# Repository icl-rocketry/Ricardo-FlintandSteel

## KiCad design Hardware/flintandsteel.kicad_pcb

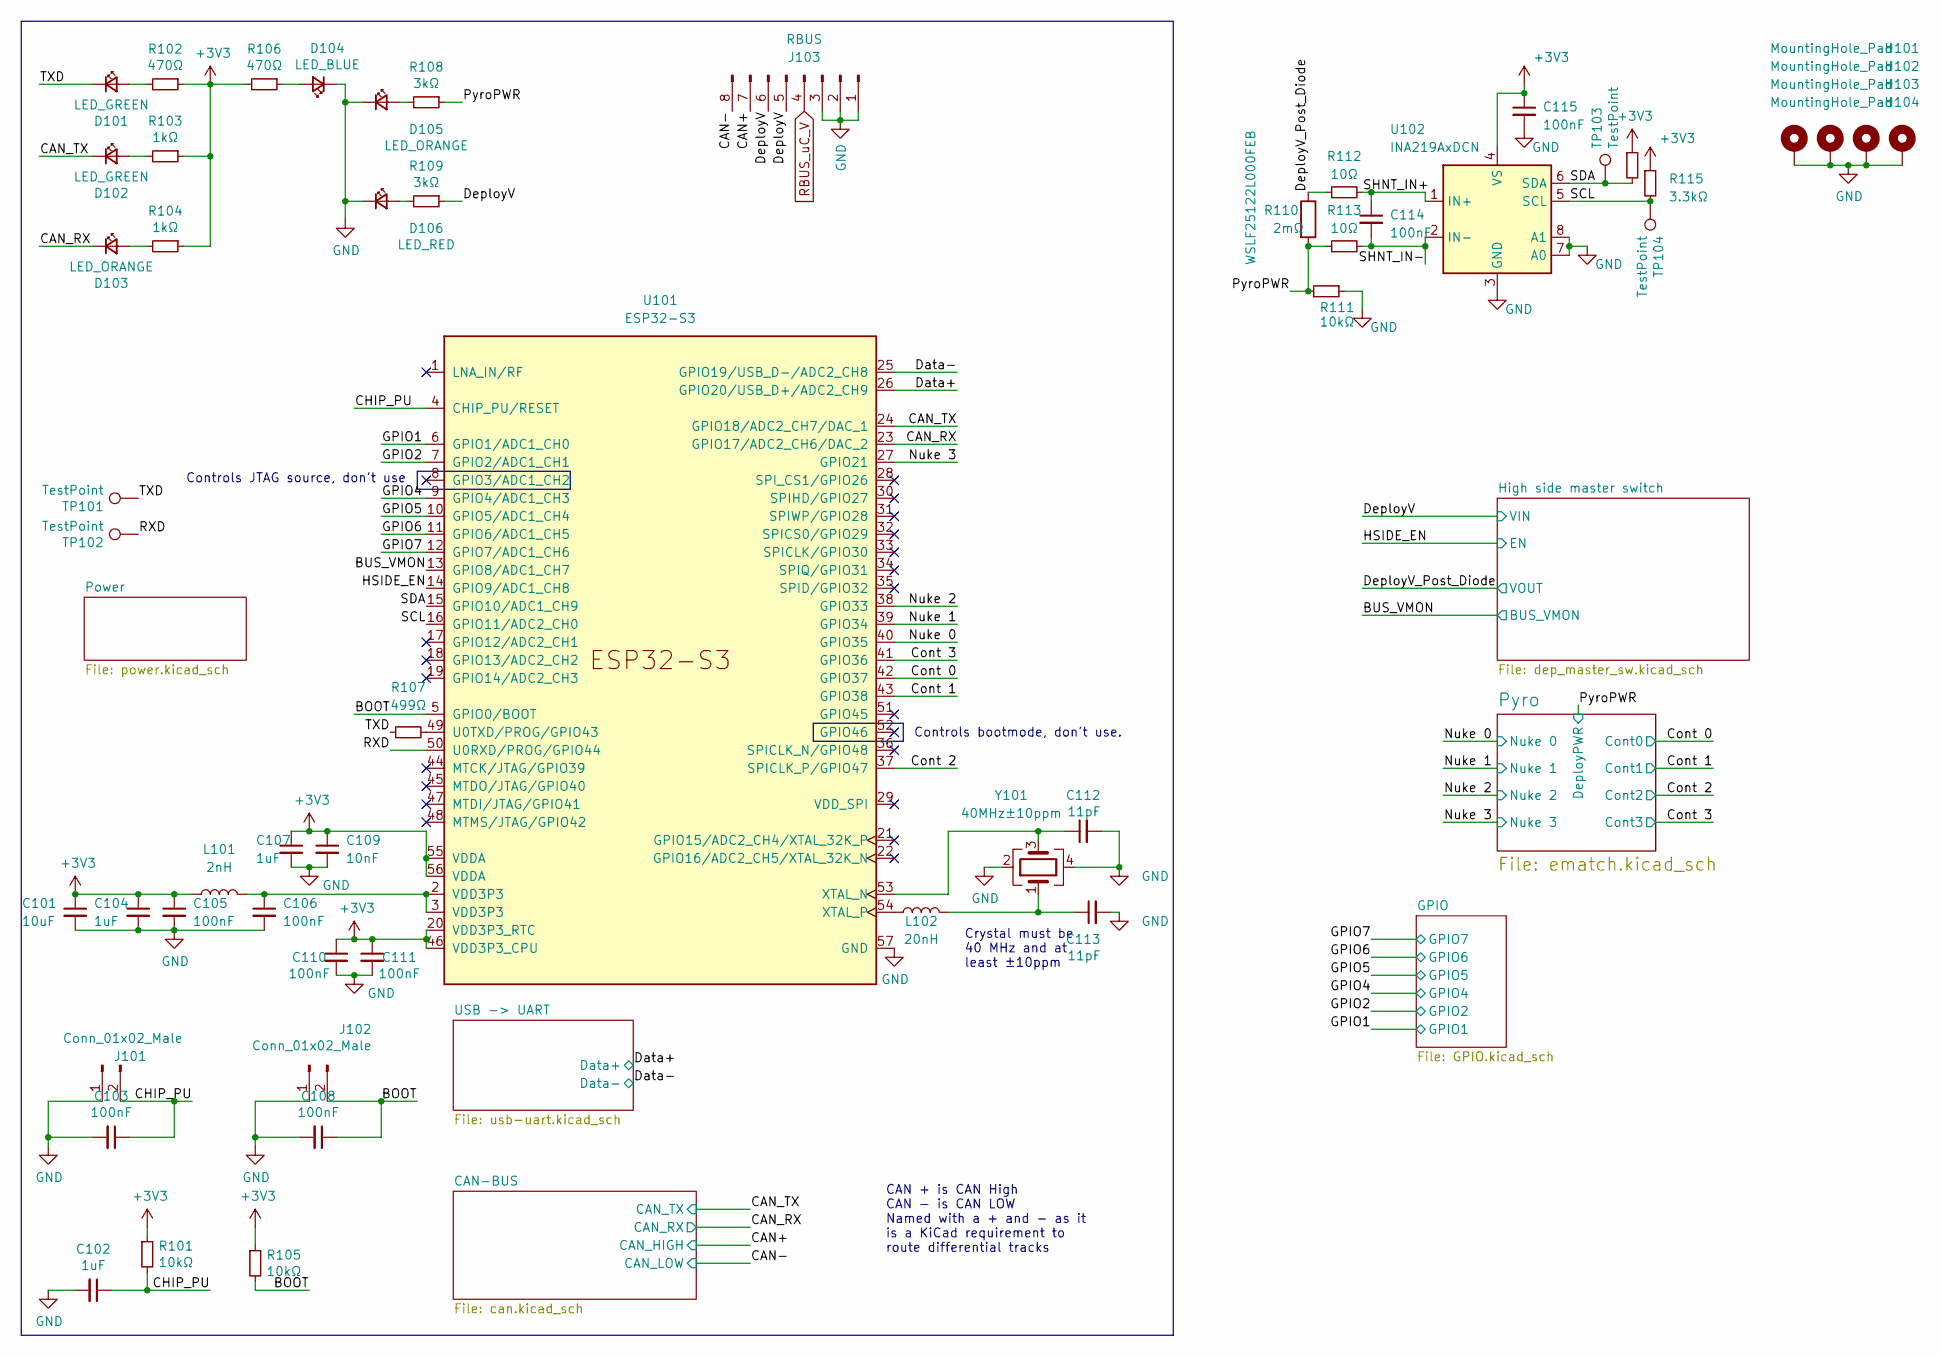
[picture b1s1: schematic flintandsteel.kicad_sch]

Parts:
C101: 10uF; C_0402_1005Metric
C102, C104, C107: 1uF; C_0402_1005Metric
C103, C105, C106, C108, C110, C111, C114, C115: 100nF; C_0402_1005Metric
C109: 10nF; C_0402_1005Metric
C112, C113: 11pF; C_0402_1005Metric
D101, D102: LED_GREEN; LED_0402_1005Metric
D103, D105: LED_ORANGE; LED_0402_1005Metric
D104: LED_BLUE; LED_0402_1005Metric
D106: LED_RED; LED_0402_1005Metric
H101, H102, H103, H104: MountingHole_Pad; MountingHole_3.2mm_M3_DIN965_Pad
J101, J102: Conn_01x02_Male; PinHeader_1x02_P2.54mm_Vertical
J103: RBUS; Molex_Mini-Fit_Jr_5569-08A2_2x04_P4.20mm_Horizontal
L101: 2nH; L_0402_1005Metric
L102: 20nH; L_0402_1005Metric
R101, R105, R111: 10kΩ; R_0402_1005Metric
R102, R106: 470Ω; R_0402_1005Metric
R103, R104: 1kΩ; R_0402_1005Metric
R107: 499Ω; R_0402_1005Metric; MPN AC0402FR-07499RL
R108, R109: 3kΩ; R_0402_1005Metric
R110: 2mΩ; R_2512_6332Metric_Pad1.40x3.35mm_HandSolder; MPN WSLF25122L000FEB
R112, R113: 10Ω; R_0402_1005Metric
R114, R115: 3.3kΩ; R_0402_1005Metric
TP101, TP102, TP103, TP104: TestPoint; TestPoint_Pad_D1.0mm
U101: ESP32-S3; QFN40P700X700X90-57N
U102: INA219AxDCN; SOT-23-8
Y101: 40MHz±10ppm; Crystal_SMD_2016-4Pin_2.0x1.6mm; MPN R940000171

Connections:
+3V3: C101.1, C104.1, C105.1, C107.1, C109.1, C110.1, C111.1, C115.1, L101.1, R101.1, R102.1, R103.1, R104.1, R105.1, R106.2, R114.1, R115.1, U101.20 (VDD3P3_RTC), U101.46 (VDD3P3_CPU), U101.55 (VDDA), U101.56 (VDDA), U102.4 (VS); also elsewhere on the board
/BOOT: C108.1, J102.2, R105.2, U101.5 (GPIO0/BOOT)
/BUS_VMON: U101.13 (GPIO8/ADC1_CH7); also elsewhere on the board
/CAN+: J103.7; also elsewhere on the board
/CAN-: J103.8; also elsewhere on the board
/CAN_RX: D103.1 (K), U101.23 (GPIO17/ADC2_CH6/DAC_2); also elsewhere on the board
/CAN_TX: D102.1 (K), U101.24 (GPIO18/ADC2_CH7/DAC_1); also elsewhere on the board
/CHIP_PU: C102.1, C103.1, J101.2, R101.2, U101.4 (CHIP_PU/RESET)
/Cont 0: U101.42 (GPIO37); also elsewhere on the board
/Cont 1: U101.43 (GPIO38); also elsewhere on the board
/Cont 2: U101.37 (SPICLK_P/GPIO47); also elsewhere on the board
/Cont 3: U101.41 (GPIO36); also elsewhere on the board
/Data+: U101.26 (GPIO20/USB_D+/ADC2_CH9); also elsewhere on the board
/Data-: U101.25 (GPIO19/USB_D-/ADC2_CH8); also elsewhere on the board
/DeployV: J103.5, J103.6, R109.1; also elsewhere on the board
/DeployV_Post_Diode: R110.1, R112.1; also elsewhere on the board
/GPIO1: U101.6 (GPIO1/ADC1_CH0); also elsewhere on the board
/GPIO2: U101.7 (GPIO2/ADC1_CH1); also elsewhere on the board
/GPIO4: U101.9 (GPIO4/ADC1_CH3); also elsewhere on the board
/GPIO5: U101.10 (GPIO5/ADC1_CH4); also elsewhere on the board
/GPIO6: U101.11 (GPIO6/ADC1_CH5); also elsewhere on the board
/GPIO7: U101.12 (GPIO7/ADC1_CH6); also elsewhere on the board
/HSIDE_EN: U101.14 (GPIO9/ADC1_CH8); also elsewhere on the board
/Nuke 0: U101.40 (GPIO35); also elsewhere on the board
/Nuke 1: U101.39 (GPIO34); also elsewhere on the board
/Nuke 2: U101.38 (GPIO33); also elsewhere on the board
/Nuke 3: U101.27 (GPIO21); also elsewhere on the board
/PyroPWR: R108.1, R110.2, R111.2, R113.1; also elsewhere on the board
/RXD: TP102.1, U101.50 (U0RXD/PROG/GPIO44)
/SCL: R115.2, TP104.1, U101.16 (GPIO11/ADC2_CH0), U102.5 (SCL)
/SDA: R114.2, TP103.1, U101.15 (GPIO10/ADC1_CH9), U102.6 (SDA)
/SHNT_IN+: C114.1, R112.2, U102.1 (IN+)
/SHNT_IN-: C114.2, R113.2, U102.2 (IN-)
/TXD: D101.1 (K), R107.1, TP101.1
GND: C101.2, C102.2, C103.2, C104.2, C105.2, C106.2, C107.2, C108.2, C109.2, C110.2, C111.2, C112.2, C113.2, C115.2, D104.1 (K), D105.1 (K), D106.1 (K), H101.1, H102.1, H103.1, H104.1, J101.1, J102.1, J103.1, J103.2, J103.3, R111.1, U101.57 (GND), U102.3 (GND), U102.7 (A0), U102.8 (A1), Y101.2, Y101.4; also elsewhere on the board
unnamed: C106.1, L101.2, U101.2 (VDD3P3), U101.3 (VDD3P3)
unnamed: C113.1, L102.2, Y101.1
unnamed: D101.2 (A), R102.2
unnamed: D102.2 (A), R103.2
unnamed: D103.2 (A), R104.2
unnamed: D104.2 (A), R106.1
unnamed: D105.2 (A), R108.2
unnamed: D106.2 (A), R109.2
unnamed: R107.2, U101.49 (U0TXD/PROG/GPIO43)
unnamed: C112.1, U101.53 (XTAL_N), Y101.3
unnamed: L102.1, U101.54 (XTAL_P)
RBUS_uC_V: J103.4; also elsewhere on the board

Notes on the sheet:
Controls bootmode, don't use.
CAN + is CAN High CAN - is CAN LOW Named with a + and - as it is a KiCad requirement to route differential tracks
Controls JTAG source, don't use
Crystal must be 40 MHz and at least ±10ppm

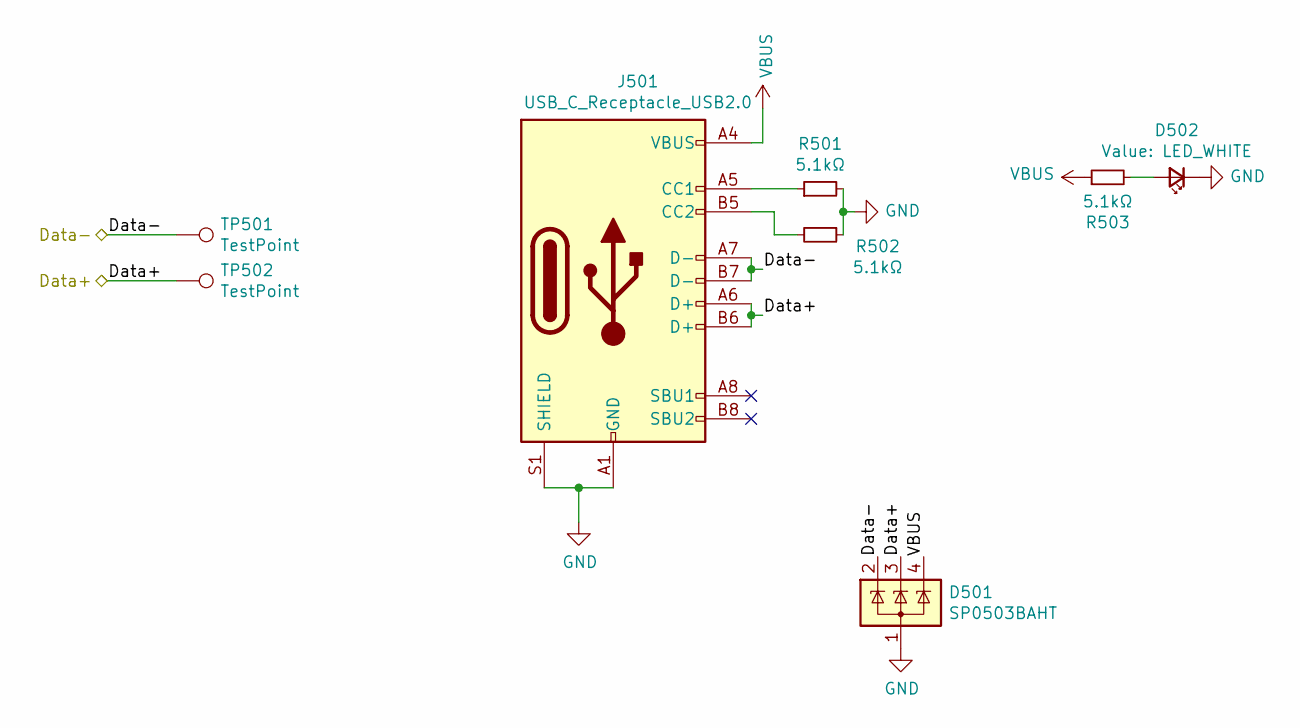
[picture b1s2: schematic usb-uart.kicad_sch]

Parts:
D501: SP0503BAHT; SOT-143
D502: LED_WHITE; LED_0402_1005Metric
J501: USB_C_Receptacle_USB2.0; USB_C_Receptacle_Palconn_UTC16-G
R501, R502, R503: 5.1kΩ; R_0402_1005Metric
TP501, TP502: TestPoint; TestPoint_Pad_D1.0mm

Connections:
/Data+: D501.3 (K), J501.A6 (D+), J501.B6 (D+), TP502.1; also elsewhere on the board
/Data-: D501.2 (K), J501.A7 (D-), J501.B7 (D-), TP501.1; also elsewhere on the board
GND: D501.1 (A), D502.1 (K), J501.A1 (GND), J501.A12 (GND), J501.B1 (GND), J501.B12 (GND), J501.S1 (SHIELD), R501.2, R502.1; also elsewhere on the board
unnamed: D502.2 (A), R503.2
unnamed: J501.A5 (CC1), R501.1
unnamed: J501.B5 (CC2), R502.2
VBUS: D501.4 (K), J501.A4 (VBUS), J501.A9 (VBUS), J501.B4 (VBUS), J501.B9 (VBUS), R503.1; also elsewhere on the board

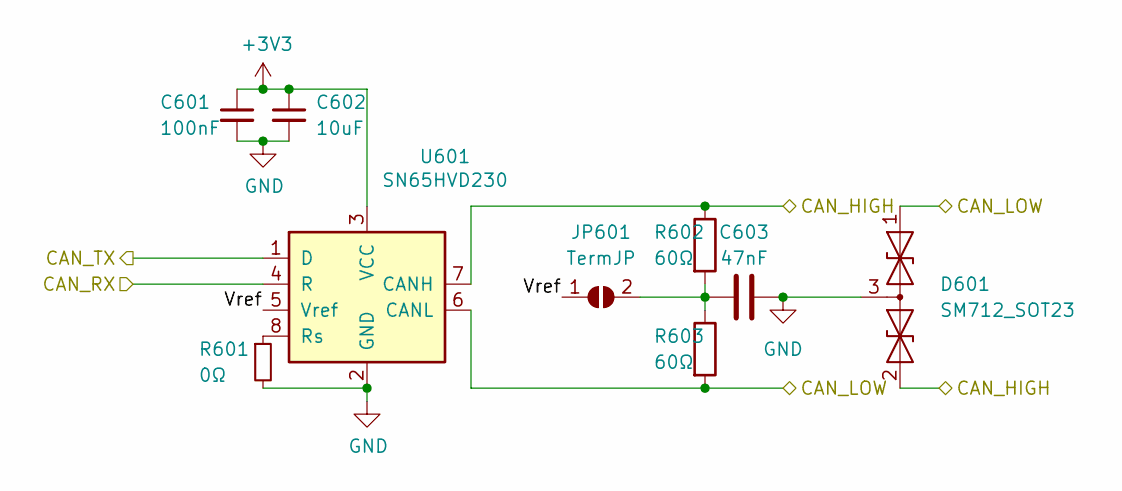
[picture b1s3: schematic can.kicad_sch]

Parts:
C601: 100nF; C_0402_1005Metric
C602: 10uF; C_0402_1005Metric
C603: 47nF; C_0402_1005Metric
D601: SM712_SOT23; SOT-23
JP601: TermJP; SmallerSolderJP
R601: 0Ω; R_0402_1005Metric
R602, R603: 60Ω; R_0603_1608Metric
U601: SN65HVD230; SOIC-8_3.9x4.9mm_P1.27mm

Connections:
+3V3: C601.1, C602.1, U601.3 (VCC); also elsewhere on the board
/CAN+: D601.2 (A2), R602.1, U601.7 (CANH); also elsewhere on the board
/CAN-: D601.1 (A1), R603.2, U601.6 (CANL); also elsewhere on the board
/CAN-BUS/Vref: JP601.1 (A), U601.5 (Vref)
/CAN_RX: U601.4 (R); also elsewhere on the board
/CAN_TX: U601.1 (D); also elsewhere on the board
GND: C601.2, C602.2, C603.2, D601.3 (common), R601.2, U601.2 (GND); also elsewhere on the board
unnamed: C603.1, JP601.2 (B), R602.2, R603.1
unnamed: R601.1, U601.8 (Rs)

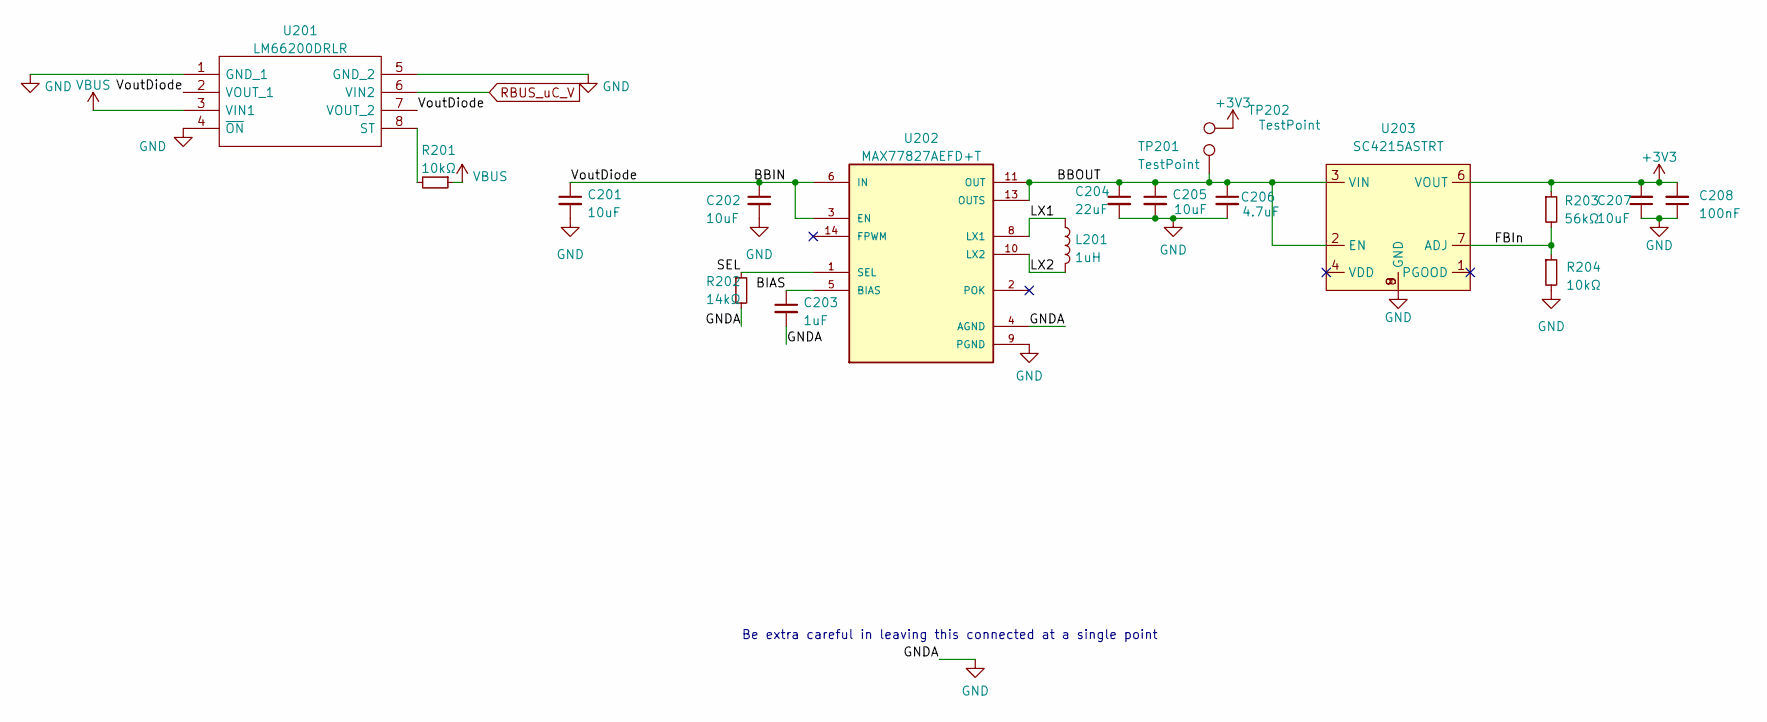
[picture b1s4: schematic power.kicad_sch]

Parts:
C201, C205, C207: 10uF; C_0402_1005Metric
C202: 10uF; C_0603_1608Metric
C203: 1uF; C_0402_1005Metric
C204: 22uF; C_0603_1608Metric
C206: 4.7uF; C_0402_1005Metric
C208: 100nF; C_0402_1005Metric
L201: 1uH; L_0805_2012Metric
R201, R204: 10kΩ; R_0402_1005Metric
R202: 14kΩ; R_0402_1005Metric
R203: 56kΩ; R_0402_1005Metric
TP201, TP202: TestPoint; TestPoint_Pad_D1.0mm
U201: LM66200DRLR; SOTFL50P160X60-8N; Manufacturer_Part_Number LM66200DRLR; Mouser Part Number 595-LM66200DRLR
U202: MAX77827AEFD+T; CONV_MAX77827AEFD+T; PARTREV B
U203: SC4215ASTRT; SOIC127P599X175-9N

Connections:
+3V3: C207.2, C208.2, R203.1, TP202.1, U203.6 (VOUT); also elsewhere on the board
/Power/BBIN: C201.1, C202.1, U201.2 (VOUT_1), U201.7 (VOUT_2), U202.3 (EN), U202.6 (IN)
/Power/BBOUT: C204.1, C205.1, C206.1, TP201.1, U202.11 (OUT), U202.13 (OUTS), U203.2 (EN), U203.3 (VIN)
/Power/BIAS: C203.1, U202.5 (BIAS)
/Power/FBIn: R203.2, R204.1, U203.7 (ADJ)
/Power/LX1: L201.1, U202.8 (LX1)
/Power/LX2: L201.2, U202.10 (LX2)
/Power/SEL: R202.1, U202.1 (SEL)
GND: C201.2, C202.2, C203.2, C204.2, C205.2, C206.2, C207.1, C208.1, R202.2, R204.2, U201.1 (GND_1), U201.4 (~ON), U201.5 (GND_2), U202.4 (AGND), U202.9 (PGND), U203.8 (GND), U203.9 (GND); also elsewhere on the board
unnamed: R201.2, U201.8 (ST)
RBUS_uC_V: U201.6 (VIN2); also elsewhere on the board
VBUS: R201.1, U201.3 (VIN1); also elsewhere on the board

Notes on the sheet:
Be extra careful in leaving this connected at a single point

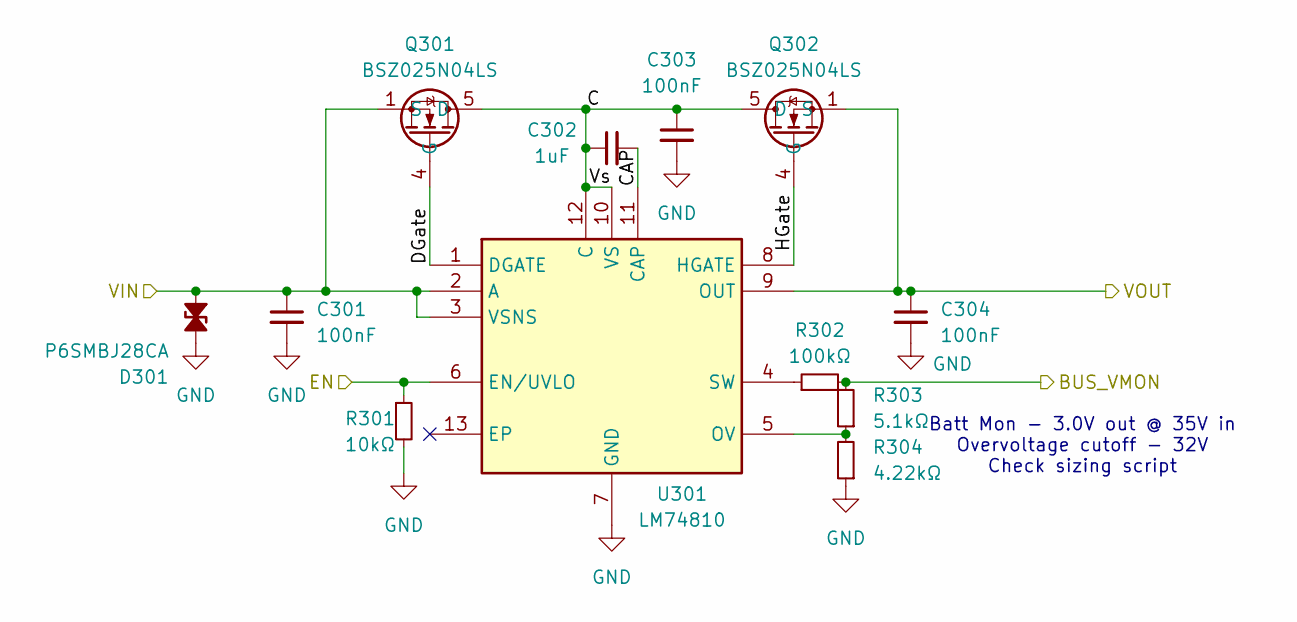
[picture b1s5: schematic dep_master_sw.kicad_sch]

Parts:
C301, C304: 100nF; C_0402_1005Metric
C302: 1uF; C_0402_1005Metric; Voltage Rating DC 50V; MPN GRT188R61H225KE13D
C303: 100nF; C_0603_1608Metric
D301: P6SMBJ28CA; D_SMA
Q301, Q302: BSZ025N04LS; Manufacturer_Part_Number BSZ025N04LS; Mouser Part Number 726-BSZ025N04LS
R301: 10kΩ; R_0402_1005Metric
R302: 100kΩ; R_0402_1005Metric
R303: 5.1kΩ; R_0402_1005Metric
R304: 4.22kΩ; R_0402_1005Metric
U301: LM74810; SON50P300X300X80-13N-D; Manufacturer_Part_Number LM74810QDRRRQ1; Mouser Part Number 595-LM74810QDRRRQ1

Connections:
/BUS_VMON: R302.2, R303.2; also elsewhere on the board
/DeployV: C301.1, D301.1 (A1), Q301.1 (S), Q301.2 (S), Q301.3 (S), Q301.A1 (S), U301.2 (A), U301.3 (VSNS); also elsewhere on the board
/DeployV_Post_Diode: C304.1, Q302.1 (S), Q302.2 (S), Q302.3 (S), Q302.A1 (S), U301.9 (OUT); also elsewhere on the board
/HSIDE_EN: R301.1, U301.6 (EN/UVLO); also elsewhere on the board
/High side master switch/C: C302.1, C303.1, Q301.5 (D), Q301.6 (D), Q301.7 (D), Q301.8 (D), Q301.A5 (D), Q302.5 (D), Q302.6 (D), Q302.7 (D), Q302.8 (D), Q302.A5 (D), U301.10 (VS), U301.12 (C)
/High side master switch/CAP: C302.2, U301.11 (CAP)
/High side master switch/DGate: Q301.4 (G), U301.1 (DGATE)
/High side master switch/HGate: Q302.4 (G), U301.8 (HGATE)
GND: C301.2, C303.2, C304.2, D301.2 (A2), R301.2, R304.1, U301.7 (GND); also elsewhere on the board
unnamed: R303.1, R304.2, U301.5 (OV)
unnamed: R302.1, U301.4 (SW)

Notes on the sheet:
Batt Mon - 3.0V out @ 35V in Overvoltage cutoff - 32V Check sizing script

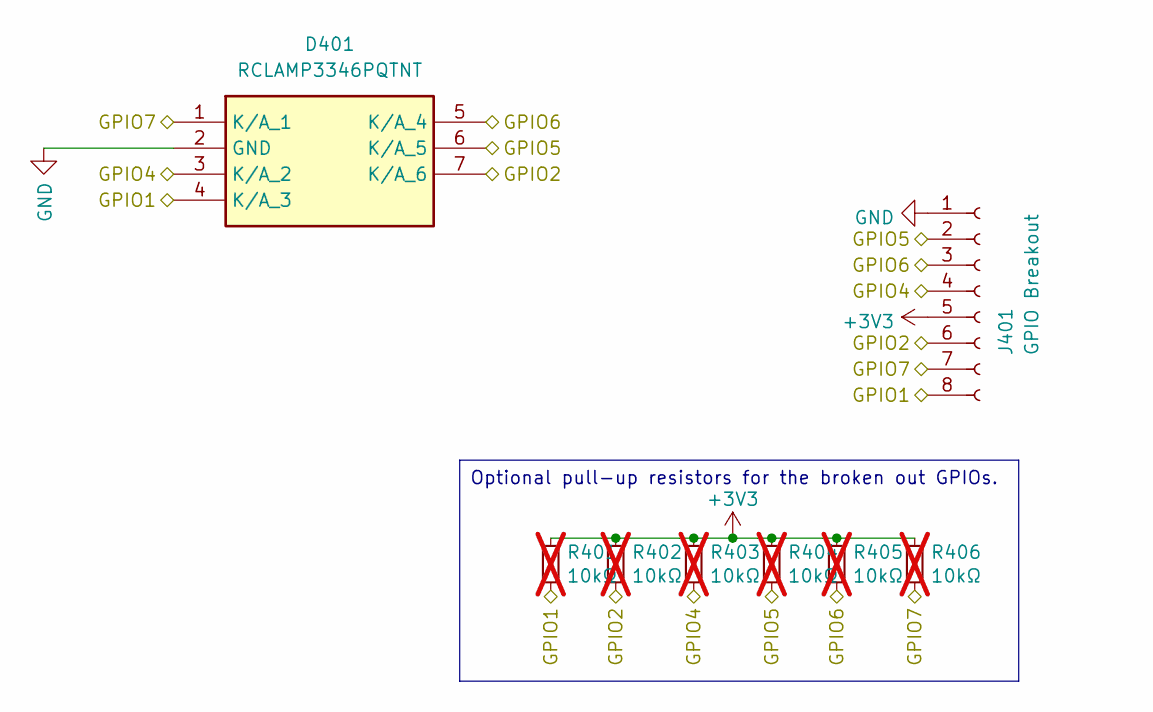
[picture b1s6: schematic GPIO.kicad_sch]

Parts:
D401: RCLAMP3346PQTNT; Mouser Part Number 947-RCLAMP3346PQTNT
J401: GPIO Breakout; PinSocket_2x04_P2.54mm_Vertical
R401, R402, R403, R404, R405, R406: 10kΩ; R_0402_1005Metric; not fitted

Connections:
+3V3: J401.5, R401.1, R402.1, R403.1, R404.1, R405.1, R406.1; also elsewhere on the board
/GPIO1: D401.4 (K/A_3), J401.8, R401.2; also elsewhere on the board
/GPIO2: D401.7 (K/A_6), J401.6, R402.2; also elsewhere on the board
/GPIO4: D401.3 (K/A_2), J401.4, R403.2; also elsewhere on the board
/GPIO5: D401.6 (K/A_5), J401.2, R404.2; also elsewhere on the board
/GPIO6: D401.5 (K/A_4), J401.3, R405.2; also elsewhere on the board
/GPIO7: D401.1 (K/A_1), J401.7, R406.2; also elsewhere on the board
GND: D401.2 (GND), J401.1; also elsewhere on the board

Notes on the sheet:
Optional pull-up resistors for the broken out GPIOs.

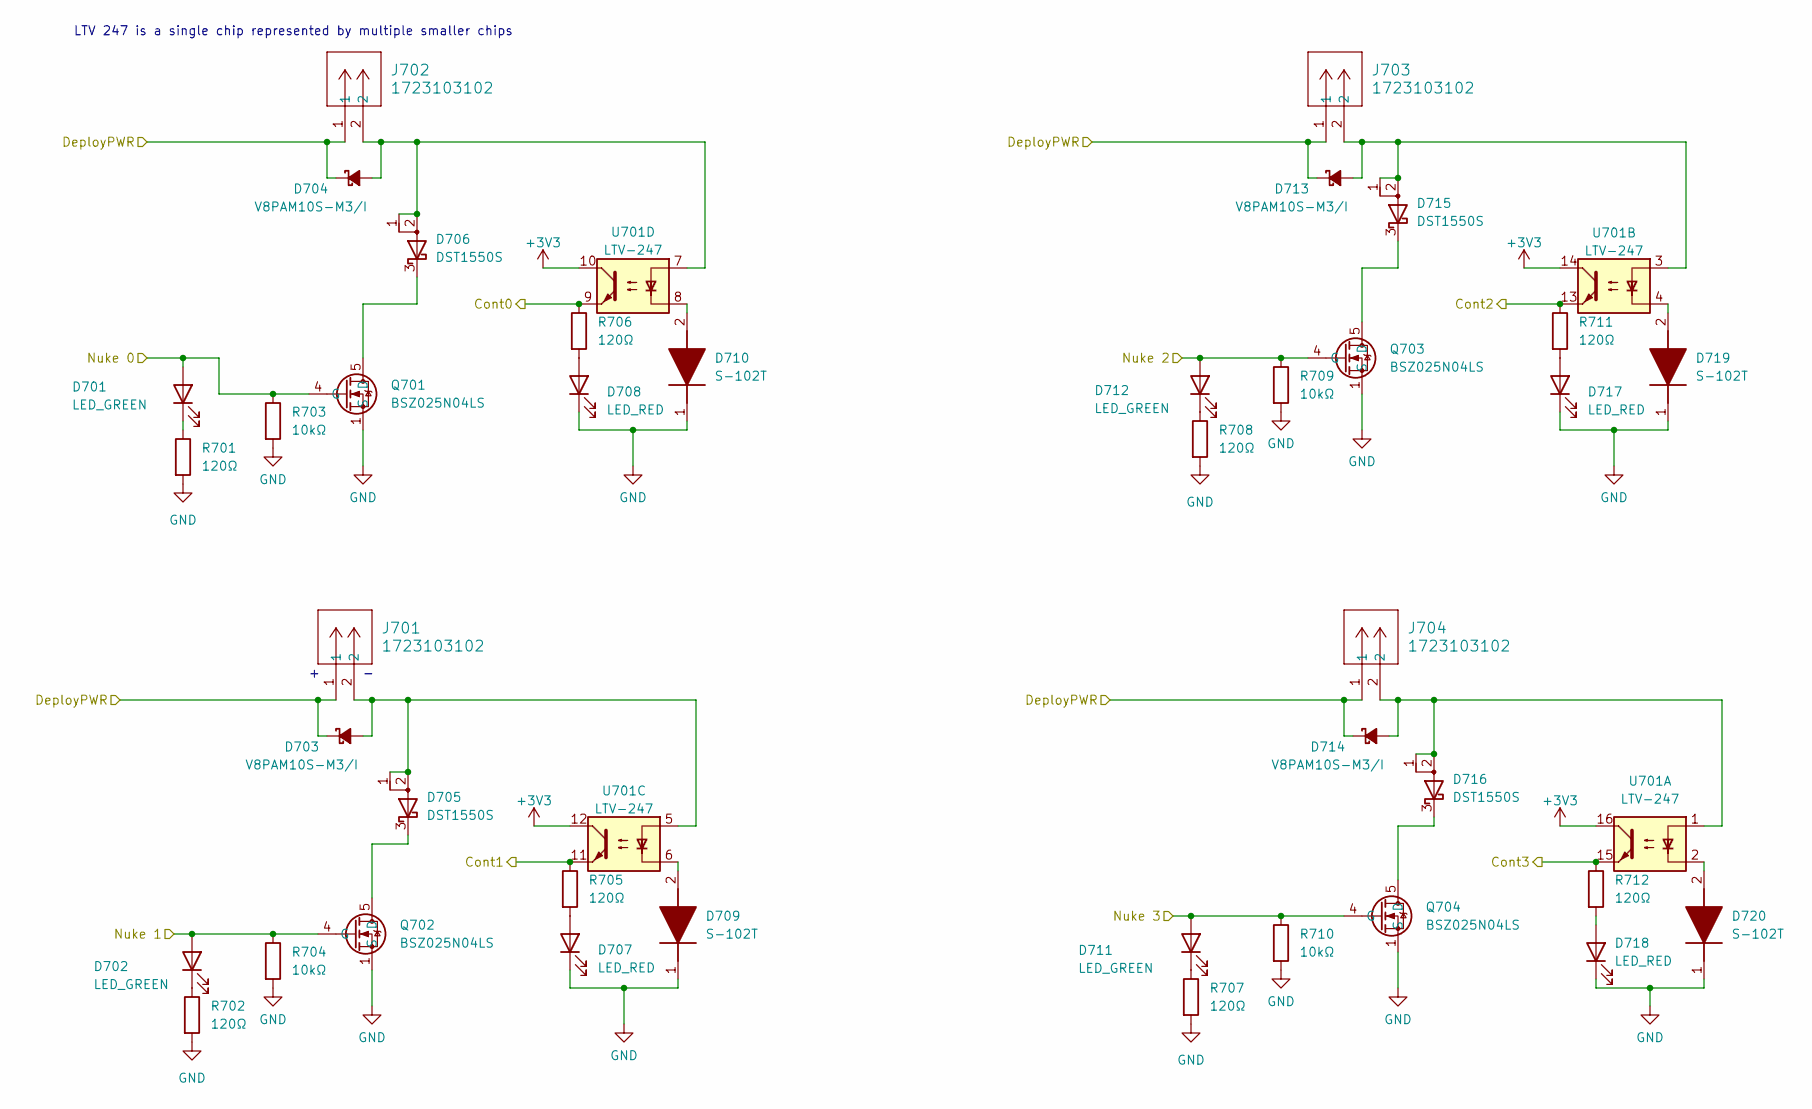
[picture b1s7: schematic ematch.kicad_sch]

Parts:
D701, D702, D711, D712: LED_GREEN; LED_0402_1005Metric
D703, D704, D713, D714: V8PAM10S-M3/I; V8PAM10SM3I
D705, D706, D715, D716: DST1550S; TO-277B
D707, D708, D717, D718: LED_RED; LED_0603_1608Metric
D709, D710, D719, D720: S-102T; SODFL3516X70N; Manufacturer_Part_Number S-102T; Mouser Part Number 954-S-102T
J701, J702, J703, J704: 1723103102; CONN_1723102000_02_MOL
Q701, Q702, Q703, Q704: BSZ025N04LS; Manufacturer_Part_Number BSZ025N04LS; Mouser Part Number 726-BSZ025N04LS
R701, R702, R707, R708: 120Ω; R_0402_1005Metric
R703, R704, R709, R710: 10kΩ; R_0402_1005Metric
R705, R706, R711, R712: 120Ω; R_0603_1608Metric
U701: LTV-247; SOP-16_4.4x10.4mm_P1.27mm

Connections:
+3V3: U701.10, U701.12, U701.14, U701.16; also elsewhere on the board
/Cont 0: R706.1, U701.9; also elsewhere on the board
/Cont 1: R705.1, U701.11; also elsewhere on the board
/Cont 2: R711.1, U701.13; also elsewhere on the board
/Cont 3: R712.1, U701.15; also elsewhere on the board
/Nuke 0: D701.2 (A), Q701.4 (G), R703.1; also elsewhere on the board
/Nuke 1: D702.2 (A), Q702.4 (G), R704.1; also elsewhere on the board
/Nuke 2: D712.2 (A), Q703.4 (G), R709.1; also elsewhere on the board
/Nuke 3: D711.2 (A), Q704.4 (G), R710.1; also elsewhere on the board
/PyroPWR: D703.1 (K), D704.1 (K), D713.1 (K), D714.1 (K), J701.1, J702.1, J703.1, J704.1; also elsewhere on the board
GND: D707.1 (K), D708.1 (K), D709.1 (K), D710.1 (K), D717.1 (K), D718.1 (K), D719.1 (K), D720.1 (K), Q701.1 (S), Q701.2 (S), Q701.3 (S), Q701.A1 (S), Q702.1 (S), Q702.2 (S), Q702.3 (S), Q702.A1 (S), Q703.1 (S), Q703.2 (S), Q703.3 (S), Q703.A1 (S), Q704.1 (S), Q704.2 (S), Q704.3 (S), Q704.A1 (S), R701.2, R702.2, R703.2, R704.2, R707.2, R708.2, R709.2, R710.2; also elsewhere on the board
unnamed: D701.1 (K), R701.1
unnamed: D702.1 (K), R702.1
unnamed: D703.2 (A), D705.1 (A), D705.2 (A), J701.2, U701.5
unnamed: D704.2 (A), D706.1 (A), D706.2 (A), J702.2, U701.7
unnamed: D705.3 (K), Q702.5 (D), Q702.6 (D), Q702.7 (D), Q702.8 (D), Q702.A5 (D)
unnamed: D706.3 (K), Q701.5 (D), Q701.6 (D), Q701.7 (D), Q701.8 (D), Q701.A5 (D)
unnamed: D707.2 (A), R705.2
unnamed: D708.2 (A), R706.2
unnamed: D709.2 (A), U701.6
unnamed: D710.2 (A), U701.8
unnamed: D711.1 (K), R707.1
unnamed: D712.1 (K), R708.1
unnamed: D713.2 (A), D715.1 (A), D715.2 (A), J703.2, U701.3
unnamed: D714.2 (A), D716.1 (A), D716.2 (A), J704.2, U701.1
unnamed: D715.3 (K), Q703.5 (D), Q703.6 (D), Q703.7 (D), Q703.8 (D), Q703.A5 (D)
unnamed: D716.3 (K), Q704.5 (D), Q704.6 (D), Q704.7 (D), Q704.8 (D), Q704.A5 (D)
unnamed: D717.2 (A), R711.2
unnamed: D718.2 (A), R712.2
unnamed: D719.2 (A), U701.4
unnamed: D720.2 (A), U701.2

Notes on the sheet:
LTV 247 is a single chip represented by multiple smaller chips

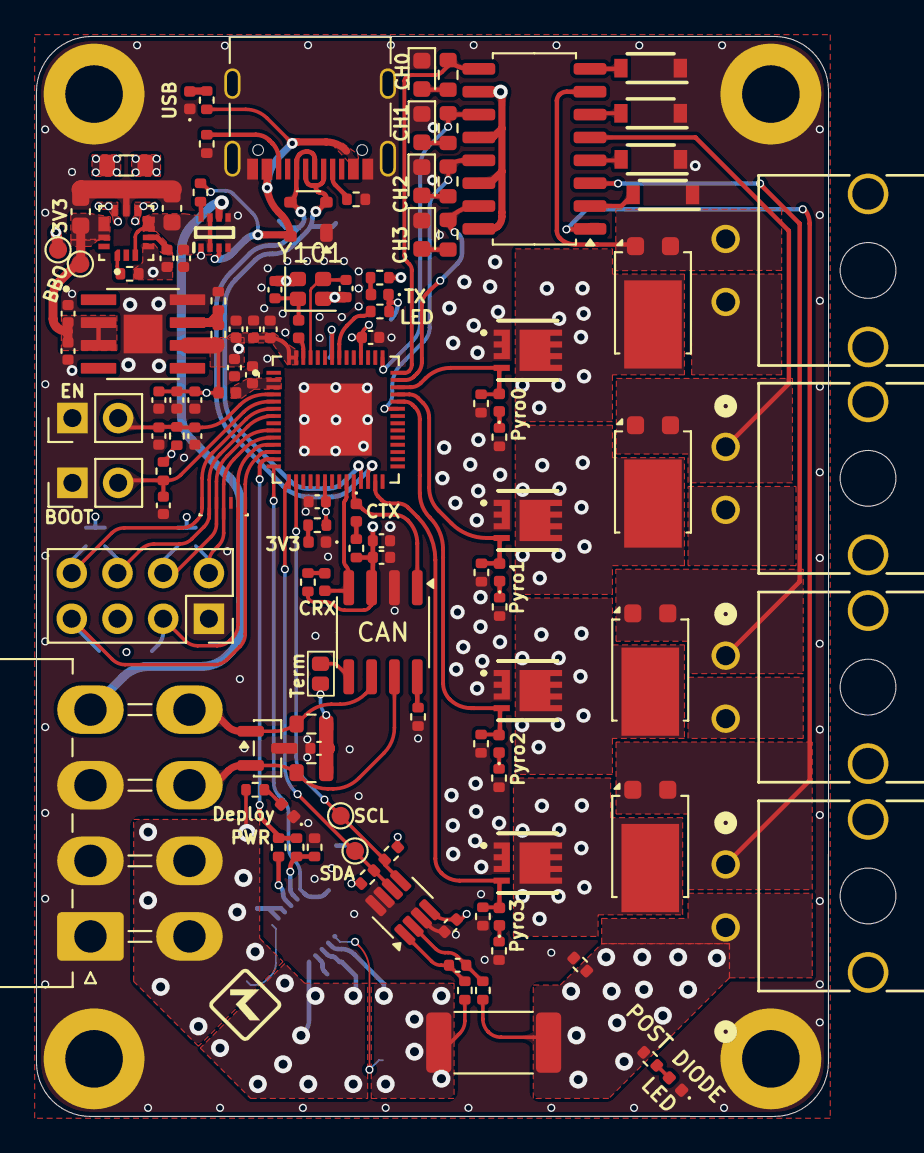
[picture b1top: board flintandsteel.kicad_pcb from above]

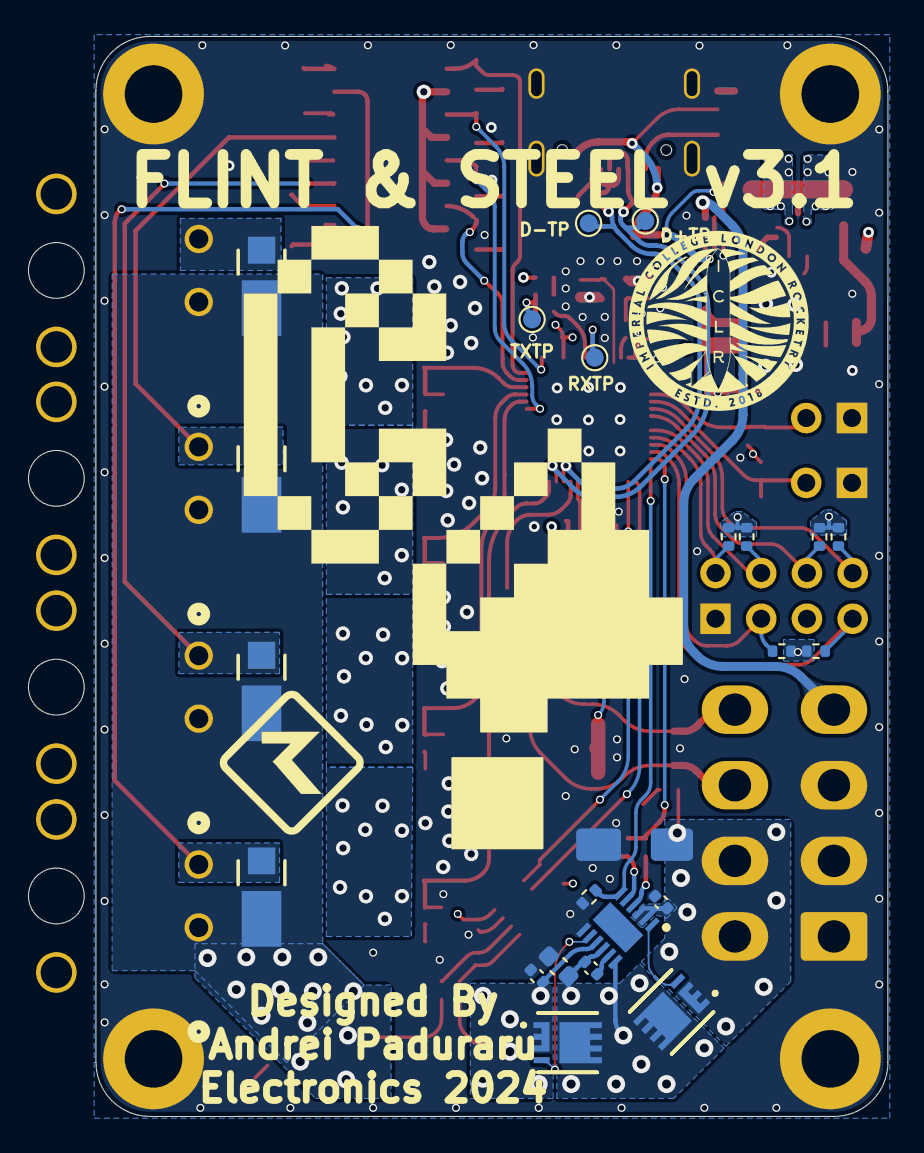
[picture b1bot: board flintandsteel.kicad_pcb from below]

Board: 4 copper layers, 44.0 x 60.0 mm, 148 parts (23 on the bottom side), 88 nets.
